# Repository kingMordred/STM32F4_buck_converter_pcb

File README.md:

# STM32F4_buck_converter_pcb

PCB design using KiCad 10.0 for an STM32F4 with a buck converter, usb connection, USART and I2c communication lines with the microcontroller and an external clock.

### Schematic overview

### Pcb overview

### Board 3D viewer

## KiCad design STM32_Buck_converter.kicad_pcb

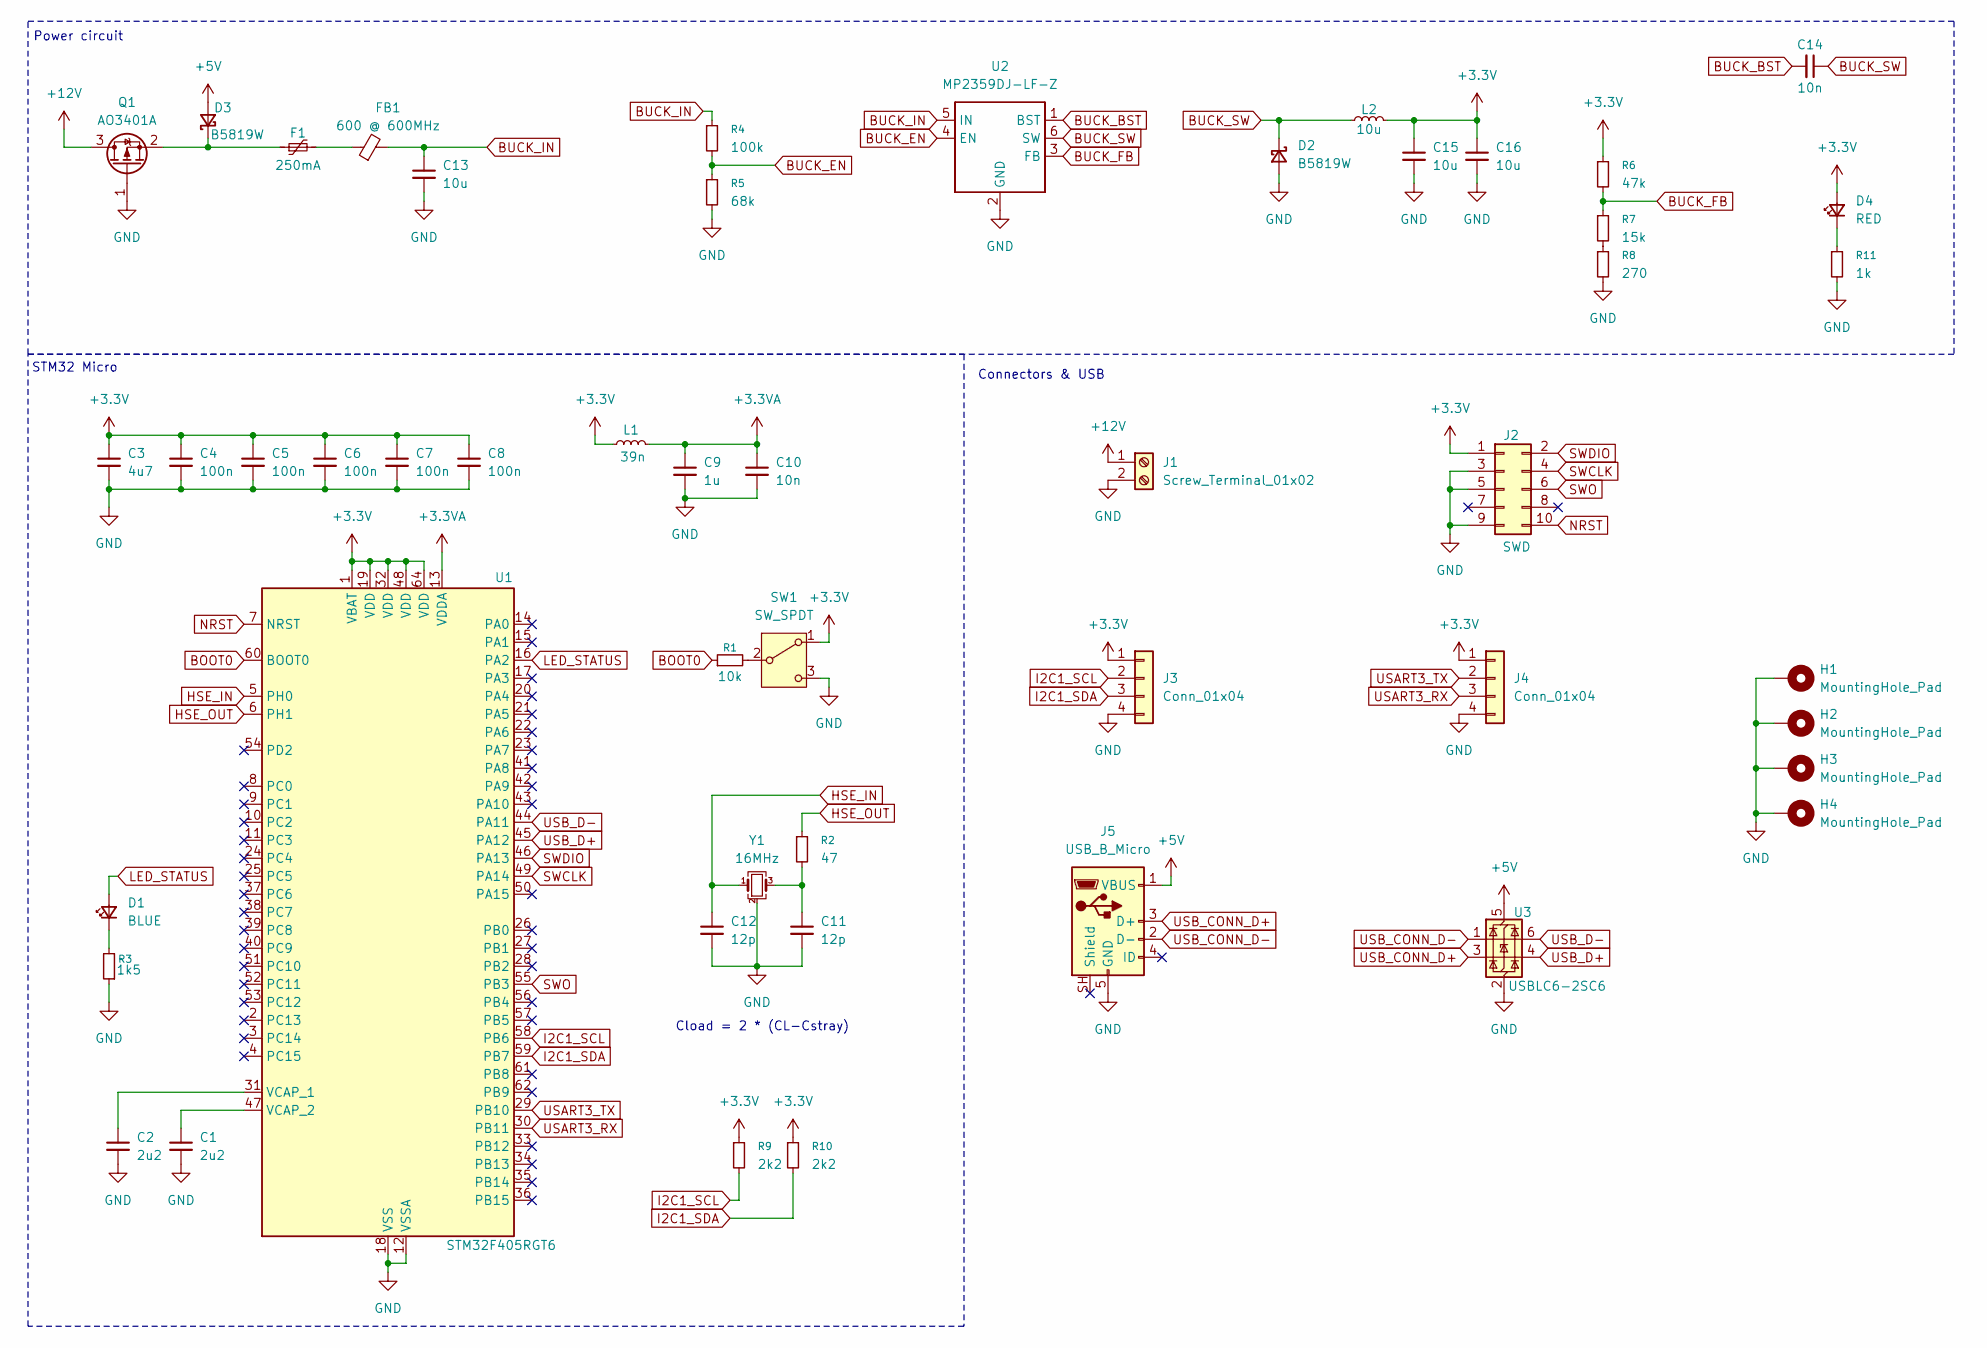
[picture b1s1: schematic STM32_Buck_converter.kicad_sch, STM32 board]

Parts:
C1, C2: 2u2; C_0603_1608Metric
C3: 4u7; C_0603_1608Metric
C4, C5, C6, C7, C8: 100n; C_0402_1005Metric
C9: 1u; C_0402_1005Metric
C10, C14: 10n; C_0402_1005Metric
C11, C12: 12p; C_0402_1005Metric
C13, C15, C16: 10u; C_1206_3216Metric
D1: BLUE; LED_0603_1608Metric
D2, D3: B5819W; D_SOD-123
D4: RED; LED_0603_1608Metric
F1: 250mA; Fuse_1206_3216Metric
FB1: 600 @ 600MHz; L_0805_2012Metric
H1, H2, H3, H4: MountingHole_Pad; MountingHole_4.3mm_M4_Pad_Via
J1: Screw_Terminal_01x02; TerminalBlock_Phoenix_PT-1,5-2-3.5-H_1x02_P3.50mm_Horizontal
J2: SWD; PinHeader_2x05_P1.27mm_Vertical_SMD
J3, J4: Conn_01x04; Molex_PicoBlade_53048-0410_1x04_P1.25mm_Horizontal
J5: USB_B_Micro; USB_Micro-B_GCT_USB3076-30-A
L1: 39n; L_0402_1005Metric
L2: 10u; L_Sunlord_MWSA0503S
Q1: AO3401A; SOT-23
R1: 10k; R_0402_1005Metric
R2: 47; R_0402_1005Metric
R3: 1k5; R_0603_1608Metric
R4: 100k; R_0603_1608Metric
R5: 68k; R_0603_1608Metric
R6: 47k; R_0603_1608Metric
R7: 15k; R_0603_1608Metric
R8: 270; R_0603_1608Metric
R9, R10: 2k2; R_0402_1005Metric
R11: 1k; R_0603_1608Metric
SW1: SW_SPDT; SW_SPDT_PCM12
U1: STM32F405RGT6; LQFP-64_10x10mm_P0.5mm
U2: MP2359DJ-LF-Z; SOT-23-6
U3: USBLC6-2SC6; SOT-23-6
Y1: 16MHz; Crystal_SMD_3225-4Pin_3.2x2.5mm

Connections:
+3.3V: C3.1, C4.1, C5.1, C6.1, C7.1, C8.1, C15.1, C16.1, D4.2 (A), J2.1, J3.1, J4.1, L1.1, L2.2, R6.1, R9.1, R10.1, SW1.1 (A), U1.1 (VBAT), U1.19 (VDD), U1.32 (VDD), U1.48 (VDD), U1.64 (VDD)
+3.3VA: C9.1, C10.1, L1.2, U1.13 (VDDA)
+5V: D3.2 (A), J5.1 (VBUS), U3.5 (VBUS)
+12V: J1.1, Q1.3 (D)
BOOT0: R1.1, U1.60 (BOOT0)
BUCK_BST: C14.2, U2.1 (BST)
BUCK_EN: R4.2, R5.1, U2.4 (EN)
BUCK_FB: R6.2, R7.1, U2.3 (FB)
BUCK_IN: C13.1, FB1.2, R4.1, U2.5 (IN)
BUCK_SW: C14.1, D2.1 (K), L2.1, U2.6 (SW)
GND: C1.2, C2.2, C3.2, C4.2, C5.2, C6.2, C7.2, C8.2, C9.2, C10.2, C11.2, C12.2, C13.2, C15.2, C16.2, D2.2 (A), H1.1 (1_1), H2.1 (1_1), H3.1 (1_1), H4.1 (1_1), J1.2, J2.3, J2.5, J2.9, J3.4, J4.4, J5.5 (GND), Q1.1 (G), R3.1, R5.2, R8.2, R11.2, SW1.3 (C), U1.12 (VSSA), U1.18 (VSS), U1.63 (VSS), U2.2 (GND), U3.2 (GND), Y1.2 (G), Y1.4 (G)
HSE_IN: C12.1, U1.5 (PH0), Y1.1
HSE_OUT: R2.1, U1.6 (PH1)
I2C1_SCL: J3.2, R9.2, U1.58 (PB6)
I2C1_SDA: J3.3, R10.2, U1.59 (PB7)
LED_STATUS: D1.2 (A), U1.16 (PA2)
NRST: J2.10, U1.7 (NRST)
unnamed: C11.1, R2.2, Y1.3
unnamed: D1.1 (K), R3.2
unnamed: D3.1 (K), F1.1, Q1.2 (S)
unnamed: D4.1 (K), R11.1
unnamed: F1.2, FB1.1
unnamed: R7.2, R8.1
unnamed: R1.2, SW1.2 (B)
unnamed: C2.1, U1.31 (VCAP_1)
unnamed: C1.1, U1.47 (VCAP_2)
SWCLK: J2.4, U1.49 (PA14)
SWDIO: J2.2, U1.46 (PA13)
SWO: J2.6, U1.55 (PB3)
USART3_RX: J4.3, U1.30 (PB11)
USART3_TX: J4.2, U1.29 (PB10)
USB_CONN_D+: J5.3 (D+), U3.3 (I/O2)
USB_CONN_D-: J5.2 (D-), U3.1 (I/O1)
USB_D+: U1.45 (PA12), U3.4 (I/O2)
USB_D-: U1.44 (PA11), U3.6 (I/O1)

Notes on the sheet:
STM32 Micro
Cload = 2 * (CL-Cstray)
Connectors & USB
Power circuit

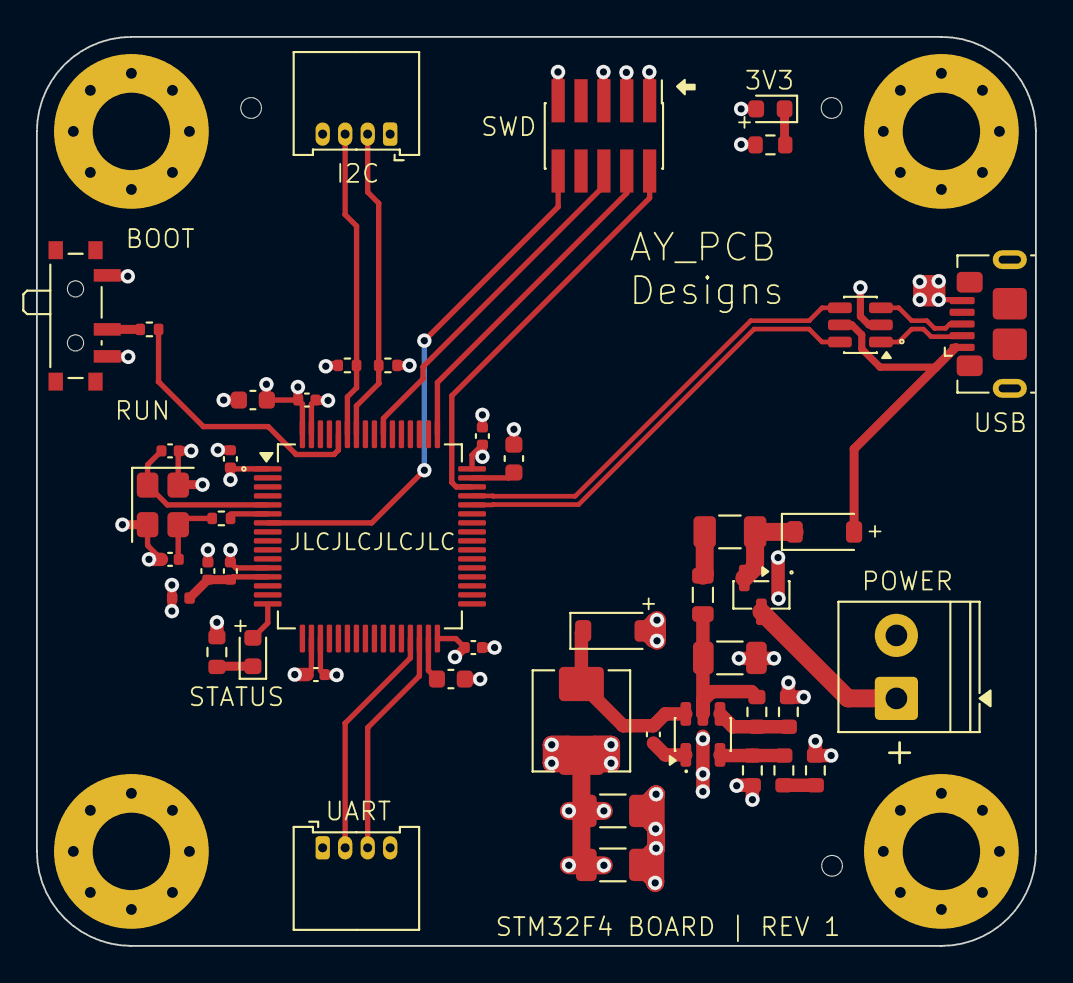
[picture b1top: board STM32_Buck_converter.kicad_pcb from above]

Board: 4 copper layers, 55.5 x 50.5 mm, 50 parts (0 on the bottom side), 35 nets.

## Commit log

2026-06-26 STM32 buck converter board pcb design - Rev 1
2026-06-26 Update README
    Added detailed project description and images for schematic, PCB, and 3D viewer.
